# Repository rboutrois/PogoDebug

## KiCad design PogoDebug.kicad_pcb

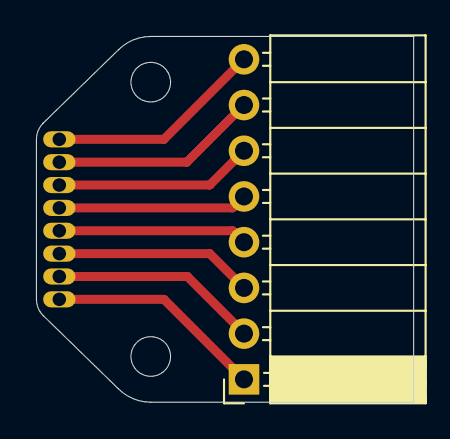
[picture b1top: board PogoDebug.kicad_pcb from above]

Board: 2 copper layers, 21.0 x 20.3 mm, 11 parts (0 on the bottom side), 8 nets.

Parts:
H1, H2: MountingHole; MountingHole_2.2mm_M2
J1, J2, J3, J4, J5, J6, J7, J8: P50-B1
J10: PinSocket_08; PinSocket_1x08_P2.54mm_Horizontal

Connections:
unnamed: J1.1, J10.1
unnamed: J2.1, J10.2
unnamed: J3.1, J10.3
unnamed: J4.1, J10.4
unnamed: J5.1, J10.5
unnamed: J6.1, J10.6
unnamed: J7.1, J10.7
unnamed: J8.1, J10.8

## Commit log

2021-03-17 First PCB commit
